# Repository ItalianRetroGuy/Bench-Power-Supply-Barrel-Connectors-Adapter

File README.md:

# Bench Power Supply Barrel Connectors Adapter

## Disclaimer
I do not take any responsibility for personal harm or property damage caused by building or using this project. Make sure to read my safety recommendations below.

## Introduction
This project allowed me to power up devices through their DC jack using my bench power supply banana plugs. I highly doubt you found this page without going through [my video](https://youtu.be/uaTE9wOTJUA) first, so you probably already know what I'm talking about!

## Use Cases
I mainly use this for powering retro consoles through their DC jacks, because of their reduced current draw and voltage requirement. It might be possible to power laptops too but only while idling, as they tend to have a much higher current draw which could exceed the capabilities of the board. Also, some laptops can detect it's not the original charger and may prevent charging the battery. Sometimes the laptop might still power on, just no charging will happen.

The polarity switch is useful for devices like the Sega Game Gear which require a different connector polarity based on their region, but generally speaking retro consoles come from a time where it was very likely to find center negative connectors. When working on a lot of them you might find yourself needing to switch polarity in between devices.

## Compatibility
This adapter can be powered via banana plugs (male). It can work with any universal connector set that can be powered via 5.5mmx2.1mm DC plugs (male), as long as you own a male-to-male 5.5mmx2.1mm barrel plug adapter.

## Recommended Connectors and Adapters (Affiliate Links)
* [Male-to-male 5.5mmx2.1mm barrel plug adapter](https://s.click.aliexpress.com/e/_DD6vQwD) <ins>***WARNING: THIS CABLE IS ONLY RATED FOR 12V @ 3A***</ins>
* [Universal connectors set](https://s.click.aliexpress.com/e/_DEg6efL) <ins>***WARNING: THESE CONNECTORS ARE ONLY RATED FOR 90W***</ins>
* If you want a better male-to-male adapter you can build it using solderable 5.5mmx2.1mm DC plugs and solder them to two wires. You can find 24V 3A ones on some websites.

## Assembly
### Instructions
Assembling this should be very straightforward, there are markings on the board that will help you place every component down properly.
* LED orientation is marked on the board like a regular diode.
* The resistors have no required orientation
* The electrolytic capacitors have the negative side marked on the board.
* The voltage regulators are TO-92 packages and they have the flat side marked down on the board.
* The DC socket cannot be placed in the wrong way.
* The polarity switch has the actuator drawn on the board but you can also rotate it to make it harder to be accidentally flicked. If you somehow prefer you can even mount it on the other side of the board.
* The banana sockets are slightly more complicated, you can see a bit of how I did in [my video](https://youtu.be/uaTE9wOTJUA) for this project. I recommend making sure the solder starts slightly poking out of the holes on the other side of the board, acting like tiny rivets. This is to ensure a very strong mount that is taking advantage of the entire board strength.
### Bill of Materials
[You can download the bill of materials from here](/bom/benchpsu_barreljack_adapter.csv)
### PCB
[You can order the PCB directly from PCBWay](https://www.pcbway.com/project/shareproject/Barrel_Connector_Adapter_for_Bench_Power_Supplies_b430900c.html), or [you can download](/grb/grb.zip) the gerber files required for manufacturing.

I recommend choosing a white or red solder mask color, as it boosts the red light coming from the LEDs.

## Instructions
### Powering a Device
* Read and become familiar with the safety information and power ratings down below
* Insert the positive banana plug coming from the bench power supply in the adapter's positive (red, or marked V+) banana socket
* Insert the negative banana plug coming from the bench power supply in the adapter's negative (black, or marked V+) banana socket
* Insert one end of a male-to-male 5.5mmx2.1mm barrel plug adapter inside the adapter's DC socket marked J3
* Attach the connector you need at the other end of the male-to-male barrel plug adapter
* Ensure the adapter board is not touching and cannot touch any conductive object or surface
* Enable power output from the bench power supply to the adapter
* Select appropriate connector wiring using the selection switch
* Plug the connector in the device which must be powered

## Safety
### Precautions
* Do not reverse the positive and negative banana plugs, the board might not survive that
* Set overvoltage protection on your bench power supply at 30V
* Optionally set a current limit or overcurrent protection of 3A on your bench power supply when using this adapter, or always be ready to cut power to the adapter board immediately
* Follow the handling recommendations listed below
* Do not exceed the power rating listed below
* Keep the board unpowered when not in use to avoid accidental shorts

### Handling
The bare adapter board must be kept away from any conductive object or surface. It has many easy to short points, and it would be best to have an enclosure for it. However, you must keep in mind that
I have not designed such an enclosure yet, and it is currently not available.

My recommendations for it would be to use simple brass standoffs, with two simple laser-cut acrylic plates above and below.
If you have a 3D printer you can probably design yourself a plastic enclosure with some slots to insert clear plastic sheets of any kind.

If you can't make yourself an enclosure, you will have to pay very close attention to where you place the board, or even wrap it in kapton tape if you're particularly forgetful about this kind of stuff.

### Power Rating
#### Important Notes
All ratings discussed here only refer to this adapter board. This doesn't apply to any kind of cable, adapter, or connector that you use with this board. Using wires, adapters, or connectors with an inferior rating can cause them to melt or catch on fire if their own rating is exceeded.

#### Absolute Maximum Rating
24V @ 3A

#### Further Details
I naturally don't have specific ratings for this board as several factors can affect it, nor have I performed any testing.

**Part #** | **Description** | **References** | **Power Rating**
--- | --- | --- | ---
SK22D15L5 | DPDT Polarity Switch | SW1 | 50V @ 3A (150W)
DC-044K-D020 | DC Socket | J3 | 24V @ 7A (168W)
HT7525-1 | LDO Voltage Regulator | U1, U2 | 30V
KS106M050C07RR0VH2FP0 | Electrolytic Capacitor | C1, C2, C3, C4 | 50V

##### According to these ratings this means that
* Exceeding 24V WILL EVENTUALLY damage the DC Socket or heating it up more than it should
* Exceeding 30V WILL damage the LDO Voltage Regulators, which might end up causing further damage to the adapter or whatever you're powering with it.
* Exceeding 50V WILL EVENTUALLY damage the Polarity Switch or heating it up more than it should
* Exceeding 50V WILL blow up the electrolytic capacitors, which could end up causing personal injury
* Exceeding 3A WILL EVENTUALLY damage the Polarity Switch or heating it up more than it should
* Exceeding 7A WILL EVENTUALLY damage the DC Socket or heating it up more than it should
* Exceeding 150W WILL EVENTUALLY damage the Polarity Switch or heating it up more than it should
* Exceeding 168W WILL EVENTUALLY damage the DC Socket or heating it up more than it should
* Exceeding ANY OF THESE, MAY cause personal injury, property damage, or start fires.

##### Should these limits somehow be exceeded
* The board MIGHT tolerate exceeding Wattage or Amperage ratings, it MIGHT tolerate exceeding 24V, but it will NEVER tolerate exceeding 30V.
* Monitor the temperature of the adapter board at all times while exceeding any limit, and make sure to be ready to cut power immediately.

## Dimensions
**Dimension** | **Value** | **Notes**
--- | --- | ---
Board Size | 66mm x 66mm
Hole Pattern Spacing | 54mm
Hole Distance From Center to Board Corner Edges | 6mm | Measured before adding fillets
Board Fillet Radius | 9mm
Mounting Hole Diameter | 3.2mm
Mounting Hole Conductive Ring Thickness | 1.2mm

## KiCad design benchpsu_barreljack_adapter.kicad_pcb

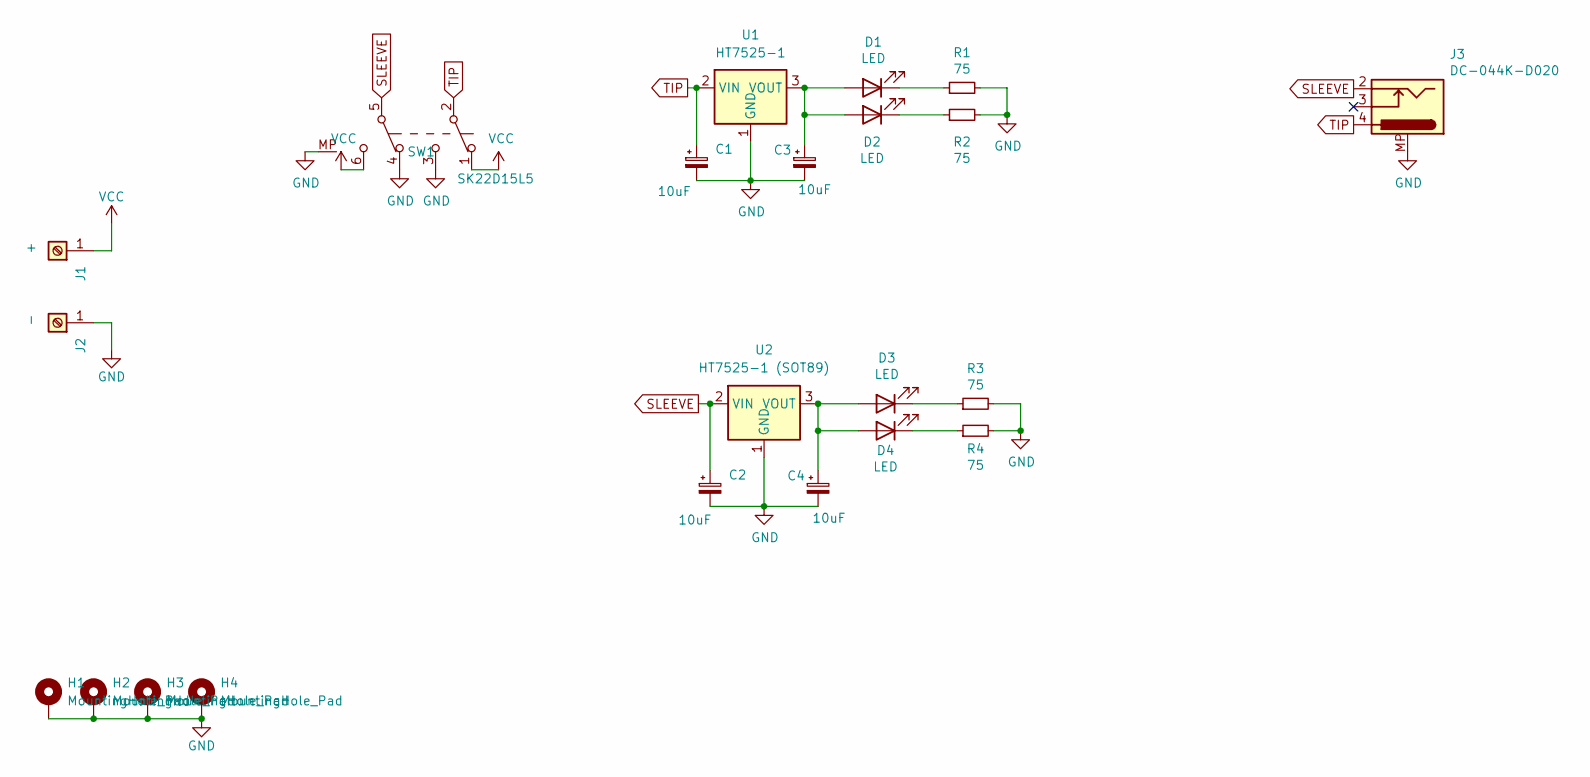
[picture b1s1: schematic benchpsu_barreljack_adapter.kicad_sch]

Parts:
C1, C2, C3, C4: 10uF; CP_Radial_D4.0mm_P1.50mm; Part Number SM1061EMB072RB
D1, D2, D3, D4: LED; LED_1210_3225Metric_Pad1.42x2.65mm_HandSolder; Part Number XL-3216SURC
H1, H2, H3, H4: MountingHole_Pad; MountingHole_3.2mm_M3_DIN965_Pad_TopBottom
J1: +; 8x10pad_stitched; Part Number 24.302.1
J2: -; 8x10pad_stitched; Part Number 24.302.2
J3: DC-044K-D020; Part Number DC-044K-D020
R1, R2, R3, R4: 75; R_1206_3216Metric_Pad1.30x1.75mm_HandSolder; Part Number FRC1206F75R0TS
SW1: SK22D15L5; Part Number SK22D15L5
U1: HT7525-1; TO-92_Inline; Part Number HT7525-1
U2: HT7525-1 (SOT89); TO-92_Inline; Part Number HT7525-1

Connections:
GND: C1.2, C2.2, C3.2, C4.2, H1.1, H2.1, H3.1, H4.1, J2.1, J3.MP, R1.2, R2.2, R3.2, R4.2, SW1.3 (C), SW1.4 (A), SW1.MP, U1.1 (GND), U2.1 (GND)
unnamed: C3.1, D1.2 (A), D2.2 (A), U1.3 (VOUT)
unnamed: D1.1 (K), R1.1
unnamed: D2.1 (K), R2.1
unnamed: C4.1, D3.2 (A), D4.2 (A), U2.3 (VOUT)
unnamed: D3.1 (K), R3.1
unnamed: D4.1 (K), R4.1
SLEEVE: C2.1, J3.2, SW1.5 (B), U2.2 (VIN)
TIP: C1.1, J3.4, SW1.2 (B), U1.2 (VIN)
VCC: J1.1, SW1.1 (A), SW1.6 (C)

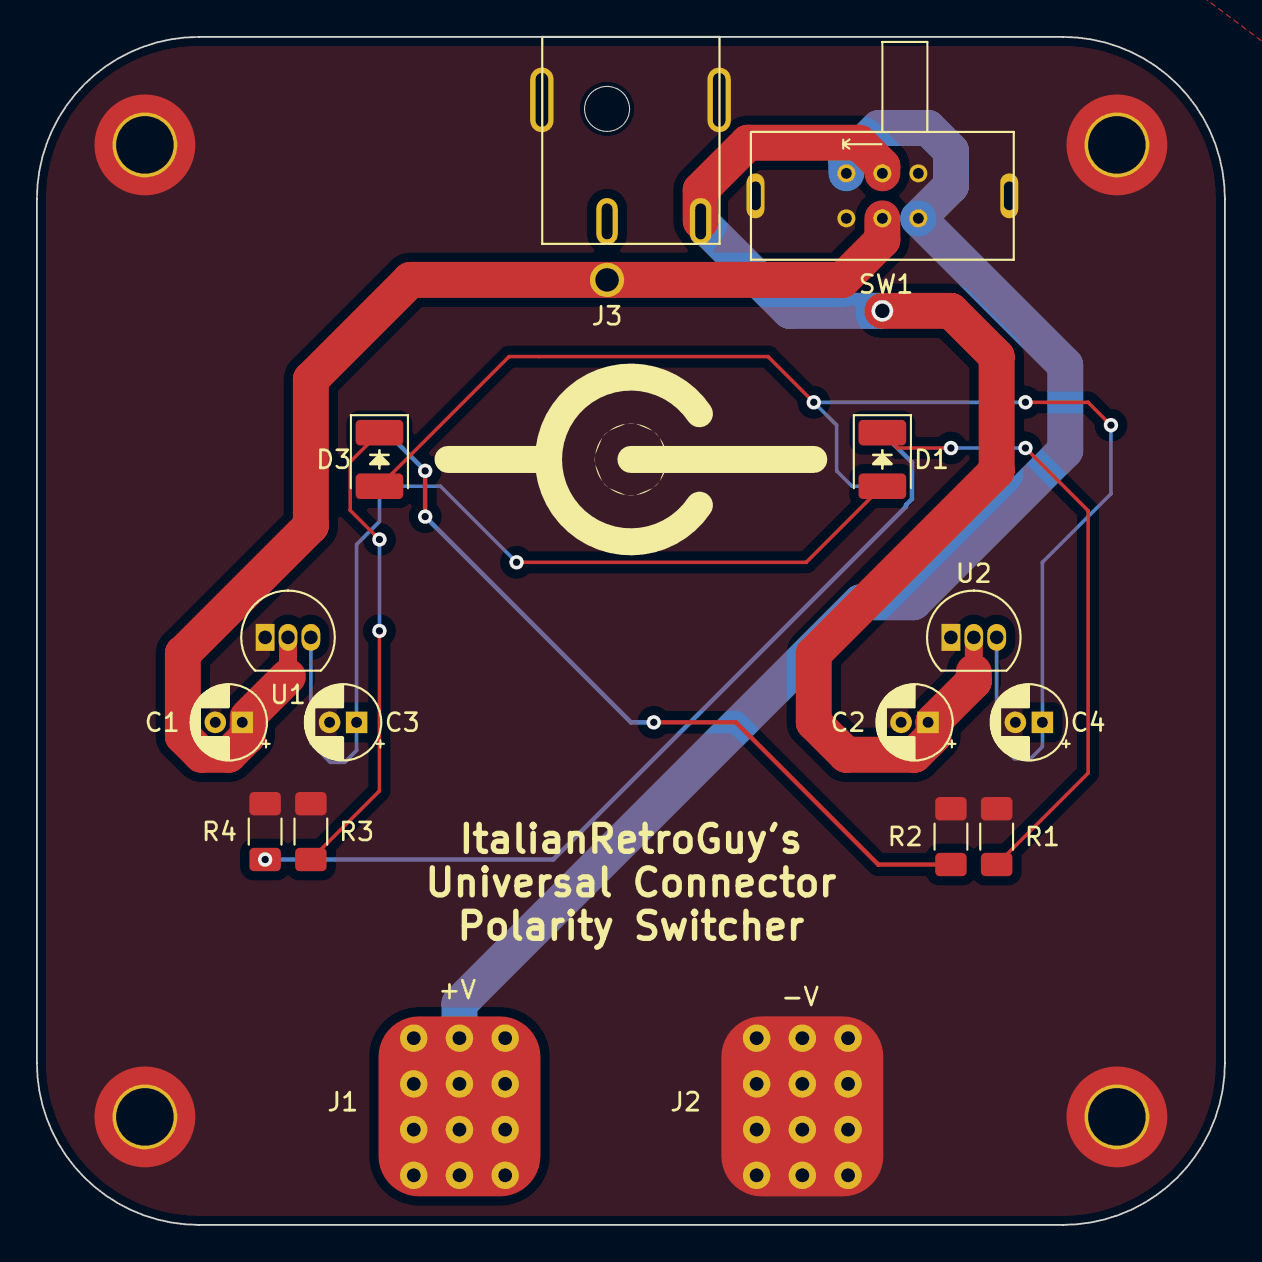
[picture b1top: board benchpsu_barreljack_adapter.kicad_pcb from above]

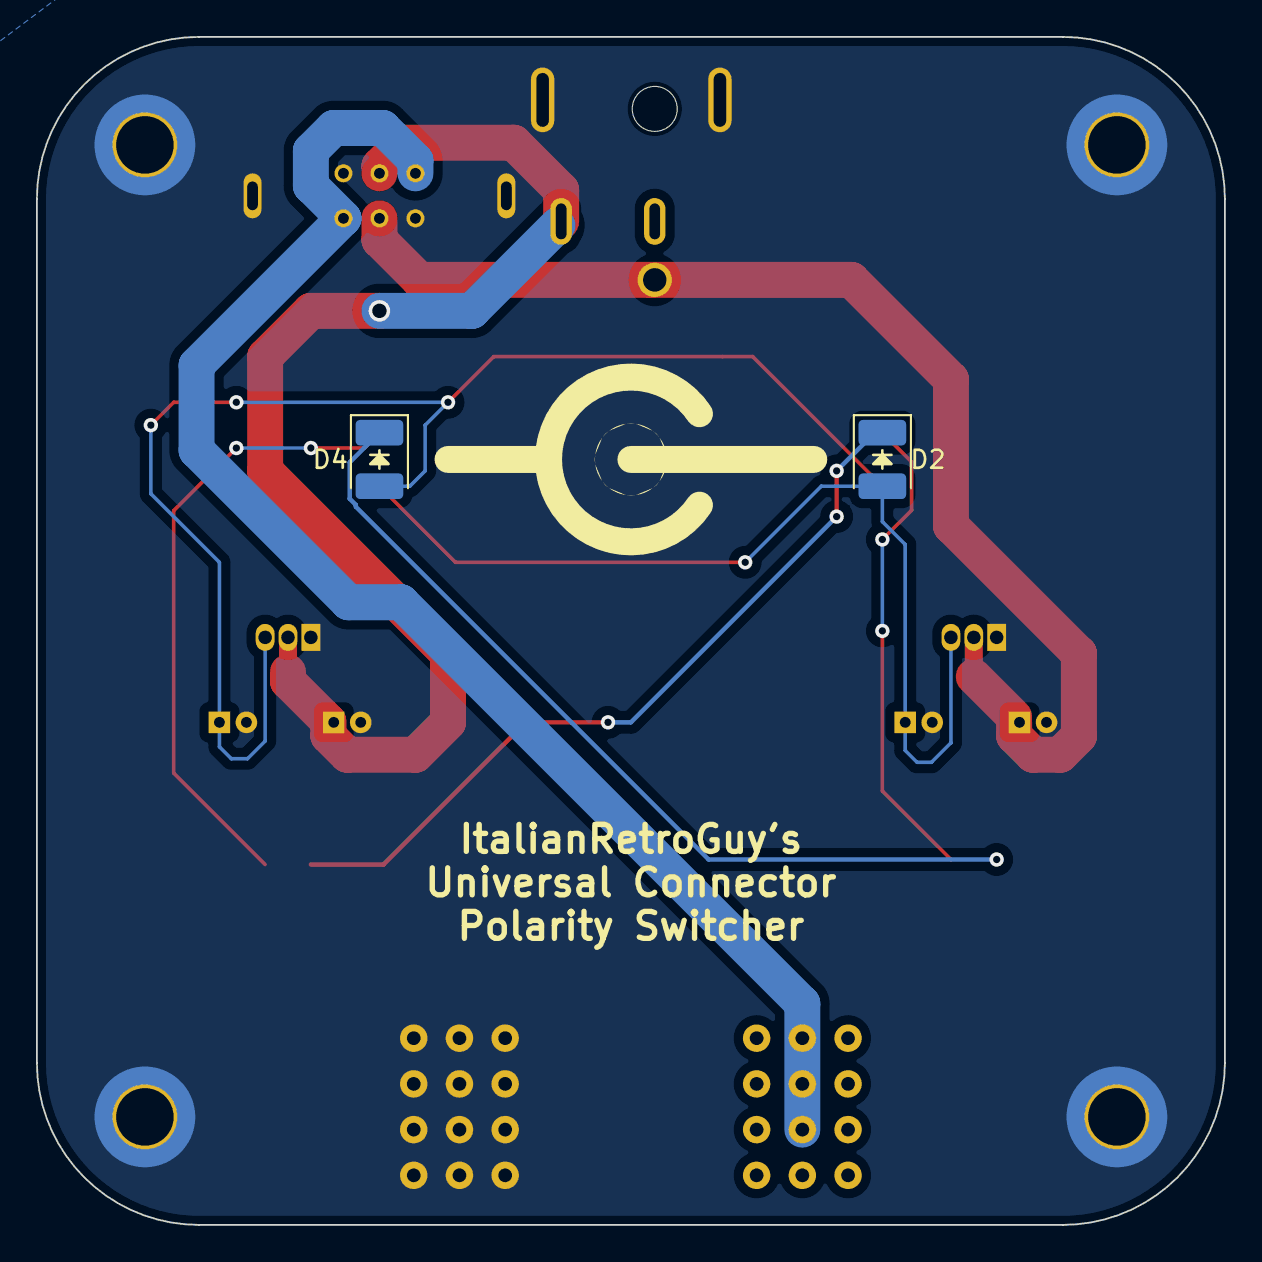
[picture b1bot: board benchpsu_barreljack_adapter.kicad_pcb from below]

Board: 2 copper layers, 66.0 x 66.0 mm, 22 parts (2 on the bottom side), 10 nets.

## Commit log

2023-05-27 Updated project
2023-05-27 Updated project for better capacitor routing
2023-05-27 Updated gerbers archive
